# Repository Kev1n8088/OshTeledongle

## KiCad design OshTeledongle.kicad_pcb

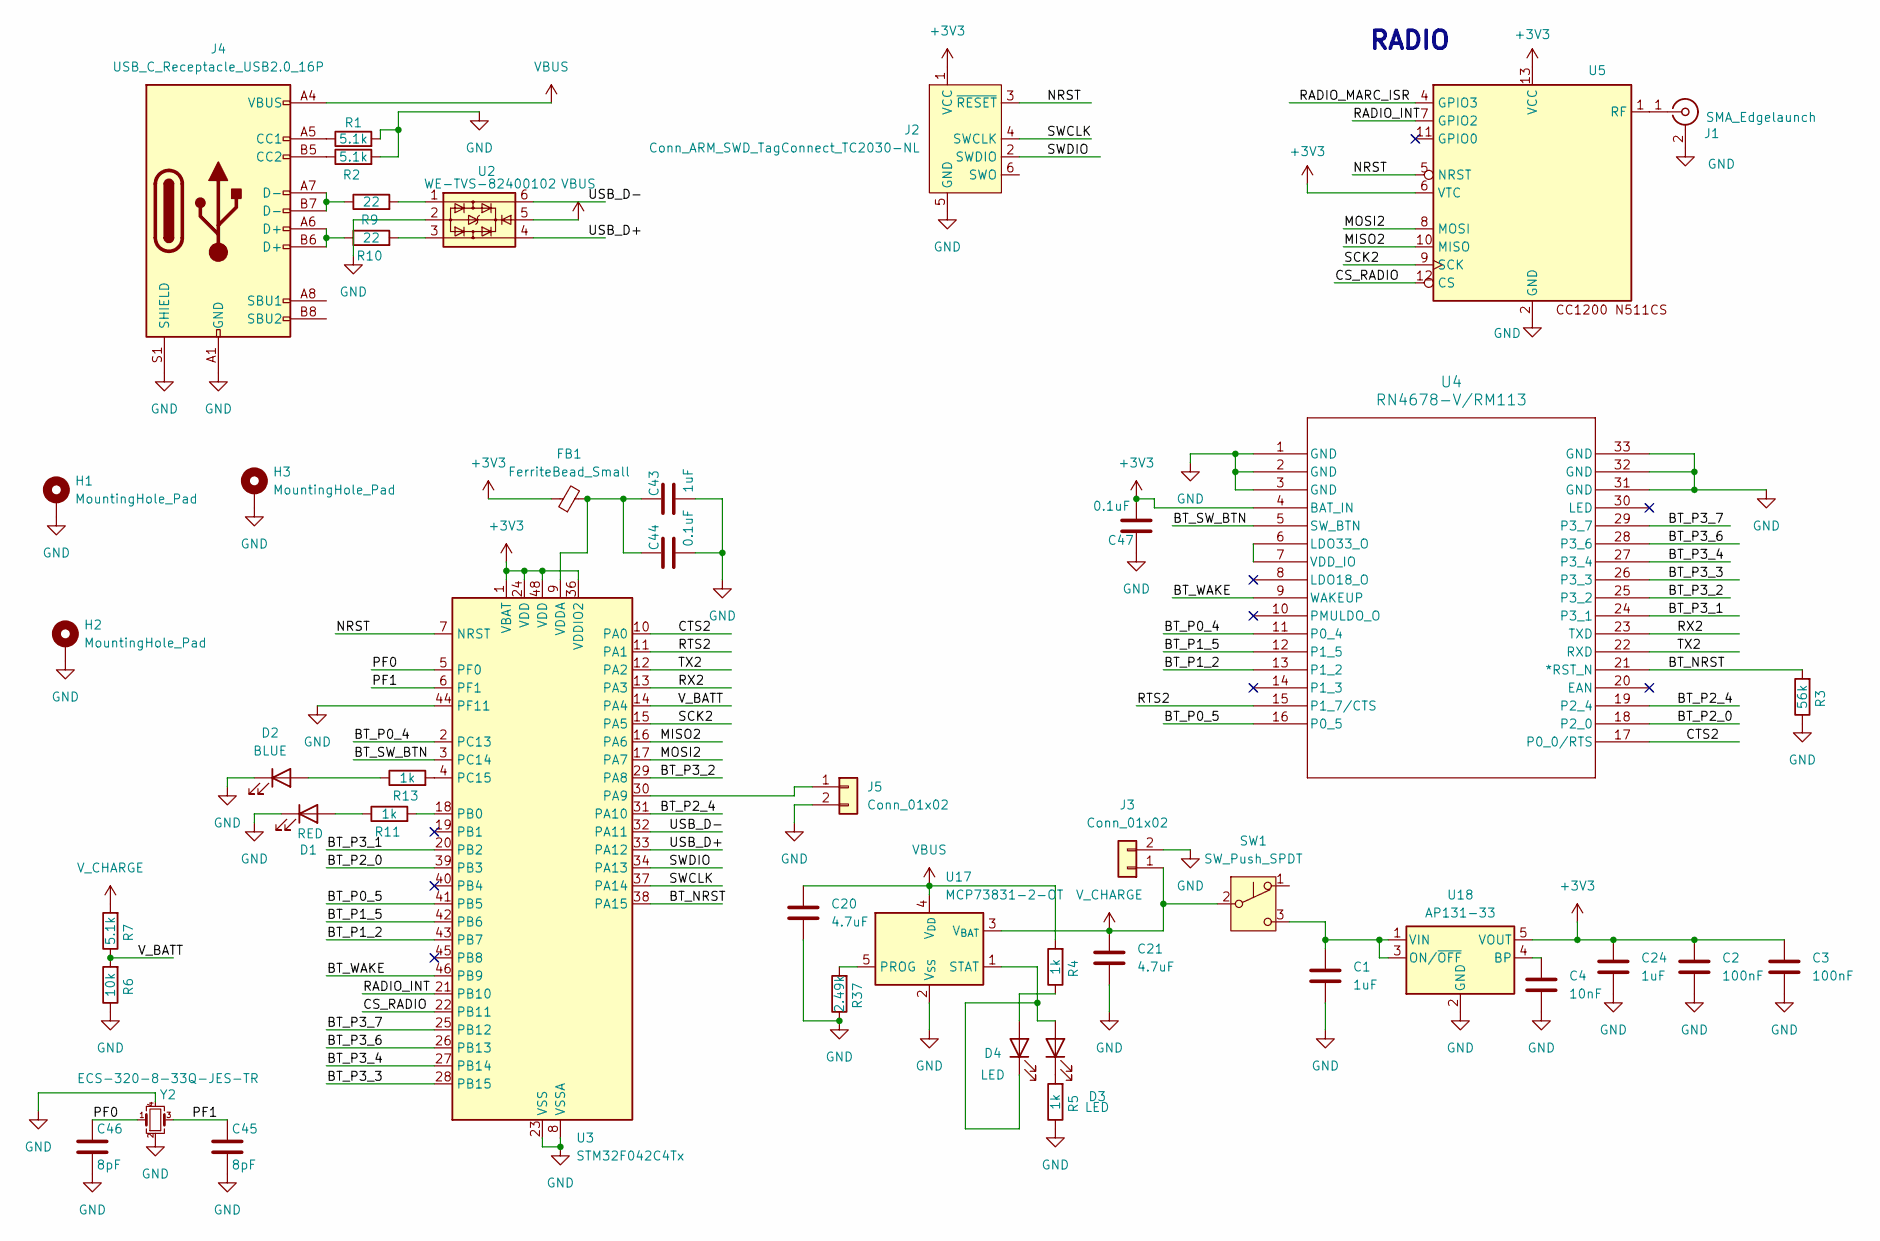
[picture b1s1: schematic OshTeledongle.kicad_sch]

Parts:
C1, C24, C43: 1uF; C_0402_1005Metric
C2, C3: 100nF; C_0402_1005Metric
C4: 10nF; C_0402_1005Metric
C20, C21: 4.7uF; C_0402_1005Metric
C44, C47: 0.1uF; C_0402_1005Metric
C45, C46: 8pF; C_0402_1005Metric
D1: RED; LED_0603_1608Metric
D2: BLUE; LED_0603_1608Metric
D3, D4: LED; LED_0603_1608Metric
FB1: FerriteBead_Small; L_0402_1005Metric
H1, H2, H3: MountingHole_Pad; MountingHole_3.2mm_M3_DIN965_Pad
J1: SMA_Edgelaunch; SMA_Amphenol_132289_EdgeMount
J2: Conn_ARM_SWD_TagConnect_TC2030-NL; Tag-Connect_TC2030-IDC-NL_2x03_P1.27mm_Vertical
J3: Conn_01x02; JST_PH_S2B-PH-K_1x02_P2.00mm_Horizontal
J4: USB_C_Receptacle_USB2.0_16P; USB_C_Receptacle_GCT_USB4105-xx-A_16P_TopMnt_Horizontal
J5: Conn_01x02; PinHeader_1x02_P2.54mm_Vertical
R1, R2, R7: 5.1k; R_0402_1005Metric
R3: 56k; R_0402_1005Metric
R4, R5, R11, R13: 1k; R_0402_1005Metric
R6: 10k; R_0402_1005Metric
R9, R10: 22; R_0402_1005Metric
R37: 2.49k; R_0402_1005Metric
SW1: SW_Push_SPDT; SW_E-Switch_EG1224_SPDT_Angled
U2: WE-TVS-82400102; SOT-23-6
U3: STM32F042C4Tx; LQFP-48_7x7mm_P0.5mm
U4: RN4678-V/RM113; RN4678_MCH
U5: N511CS
U17: MCP73831-2-OT; SOT-23-5
U18: AP131-33; SOT-23-5
Y2: ECS-320-8-33Q-JES-TR; Crystal_SMD_Abracon_ABM8G-4Pin_3.2x2.5mm

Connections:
+3V3: C2.2, C3.2, C24.2, C47.1, FB1.1, J2.1 (VCC), U3.1 (VBAT), U3.24 (VDD), U3.36 (VDDIO2), U3.48 (VDD), U4.4 (BAT_IN), U5.6 (VTC), U5.13 (VCC), U18.5 (VOUT)
/BT_NRST: R3.2, U3.38 (PA15), U4.21 (*RST_N)
/BT_P0_4: U3.2 (PC13), U4.11 (P0_4)
/BT_P0_5: U3.41 (PB5), U4.16 (P0_5)
/BT_P1_2: U3.43 (PB7), U4.13 (P1_2)
/BT_P1_5: U3.42 (PB6), U4.12 (P1_5)
/BT_P2_0: U3.39 (PB3), U4.18 (P2_0)
/BT_P2_4: U3.31 (PA10), U4.19 (P2_4)
/BT_P3_1: U3.20 (PB2), U4.24 (P3_1)
/BT_P3_2: U3.29 (PA8), U4.25 (P3_2)
/BT_P3_3: U3.28 (PB15), U4.26 (P3_3)
/BT_P3_4: U3.27 (PB14), U4.27 (P3_4)
/BT_P3_6: U3.26 (PB13), U4.28 (P3_6)
/BT_P3_7: U3.25 (PB12), U4.29 (P3_7)
/BT_SW_BTN: U3.3 (PC14), U4.5 (SW_BTN)
/BT_WAKE: U3.46 (PB9), U4.9 (WAKEUP)
/CS_RADIO: U3.22 (PB11), U5.12 (CS)
/CTS2: U3.10 (PA0), U4.17 (P0_0/RTS)
/MISO2: U3.16 (PA6), U5.10 (MISO)
/MOSI2: U3.17 (PA7), U5.8 (MOSI)
/NRST: J2.3 (~RESET), U3.7 (NRST), U5.5 (NRST)
/PF0: C46.2, U3.5 (PF0), Y2.1
/PF1: C45.2, U3.6 (PF1), Y2.3
/RADIO_INT: U3.21 (PB10), U5.7 (GPIO2)
/RADIO_MARC_ISR: U5.4 (GPIO3)
/RTS2: U3.11 (PA1), U4.15 (P1_7/CTS)
/RX2: U3.13 (PA3), U4.23 (TXD)
/SCK2: U3.15 (PA5), U5.9 (SCK)
/SWCLK: J2.4 (SWCLK), U3.37 (PA14)
/SWDIO: J2.2 (SWDIO), U3.34 (PA13)
/TX2: U3.12 (PA2), U4.22 (RXD)
/USB_D+: U2.4, U3.33 (PA12)
/USB_D-: U2.6, U3.32 (PA11)
/V_BATT: R6.2, R7.1, U3.14 (PA4)
GND: C1.1, C2.1, C3.1, C4.1, C20.1, C21.1, C24.1, C43.1, C44.1, C45.1, C46.1, C47.2, D1.1 (K), D2.1 (K), H1.1, H2.1, H3.1, J1.2 (Ext), J2.5 (GND), J3.2, J4.A1 (GND), J4.A12 (GND), J4.B1 (GND), J4.B12 (GND), J4.S1 (SHIELD), J5.2, R1.2, R2.2, R3.1, R5.1, R6.1, R37.1, U2.2, U3.8 (VSSA), U3.23 (VSS), U3.35 (VSS), U3.44 (PF11), U3.47 (VSS), U4.1 (GND), U4.2 (GND), U4.3 (GND), U4.31 (GND), U4.32 (GND), U4.33 (GND), U5.2 (GND), U5.3 (GND), U5.14 (GND), U17.2 (V_{SS}), U18.2 (GND), Y2.2, Y2.4
unnamed: D1.2 (A), R11.1
unnamed: D2.2 (A), R13.1
unnamed: D3.2 (A), D4.1 (K), U17.1 (STAT)
unnamed: D3.1 (K), R5.2
unnamed: D4.2 (A), R4.1
unnamed: J1.1 (In), U5.1 (RF)
unnamed: J4.A5 (CC1), R1.1
unnamed: J4.B5 (CC2), R2.1
unnamed: J4.A6 (D+), J4.B6 (D+), R10.1
unnamed: J4.A7 (D-), J4.B7 (D-), R9.1
unnamed: J5.1, U3.30 (PA9)
unnamed: R9.2, U2.1
unnamed: R10.2, U2.3
unnamed: C1.2, SW1.3 (C), U18.1 (VIN), U18.3 (ON/~OFF)
unnamed: R11.2, U3.18 (PB0)
unnamed: R13.2, U3.4 (PC15)
unnamed: C43.2, C44.2, FB1.2, U3.9 (VDDA)
unnamed: U4.6 (LDO33_O), U4.7 (VDD_IO)
unnamed: R37.2, U17.5 (PROG)
unnamed: C4.2, U18.4 (BP)
VBUS: C20.2, J4.A4 (VBUS), J4.A9 (VBUS), J4.B4 (VBUS), J4.B9 (VBUS), R4.2, U2.5, U17.4 (V_{DD})
V_CHARGE: C21.2, J3.1, R7.2, SW1.2 (B), U17.3 (V_{BAT})

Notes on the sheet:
RADIO

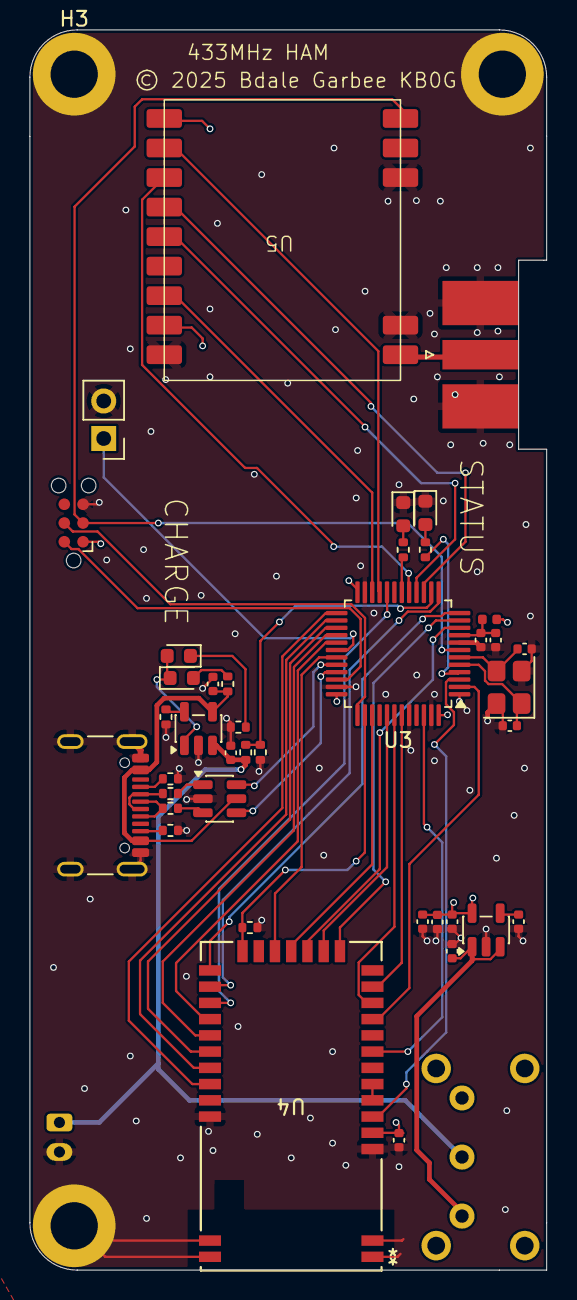
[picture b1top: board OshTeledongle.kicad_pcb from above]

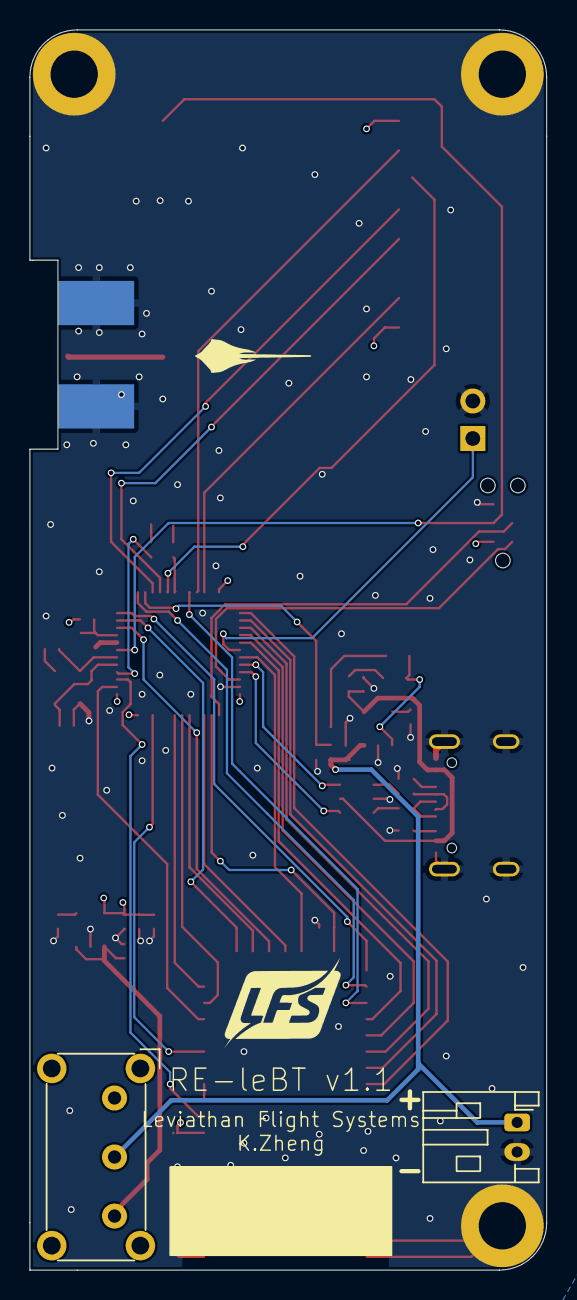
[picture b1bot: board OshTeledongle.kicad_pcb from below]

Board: 4 copper layers, 35.0 x 84.0 mm, 45 parts (2 on the bottom side), 56 nets.

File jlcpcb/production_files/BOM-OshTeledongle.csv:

Comment,Designator,Footprint,LCSC,Quantity
0.1uF,"C44,C47",C_0402_1005Metric,C1525,2
100nF,"C2,C3",C_0402_1005Metric,C1525,2
10k,R6,R_0402_1005Metric,C25744,1
10nF,C4,C_0402_1005Metric,C15195,1
1k,"R11,R13,R4,R5",R_0402_1005Metric,C11702,4
1uF,"C1,C24,C43",C_0402_1005Metric,C52923,3
2.49k,R37,R_0402_1005Metric,C145071,1
22,"R10,R9",R_0402_1005Metric,C25092,2
4.7uF,"C20,C21",C_0402_1005Metric,C23733,2
5.1k,"R1,R2,R7",R_0402_1005Metric,C25905,3
56k,R3,R_0402_1005Metric,C25794,1
8pF,"C45,C46",C_0402_1005Metric,C1549,2
AP131-33,U18,SOT-23-5,C6864,1
BLUE,D2,LED_0603_1608Metric,C2290,1
ECS-320-8-33Q-JES-TR,Y2,Crystal_SMD_Abracon_ABM8G-4Pin_3.2x2.5mm,C3034370,1
FerriteBead_Small,FB1,L_0402_1005Metric,C269768,1
LED,D3,LED_0603_1608Metric,C2286,1
LED,D4,LED_0603_1608Metric,C2290,1
MCP73831-2-OT,U17,SOT-23-5,C424093,1
RED,D1,LED_0603_1608Metric,C2286,1
STM32F042C4Tx,U3,LQFP-48_7x7mm_P0.5mm,C88447,1
USB_C_Receptacle_USB2.0_16P,J4,USB_C_Receptacle_GCT_USB4105-xx-A_16P_TopMnt_Horizontal,C3020560,1
WE-TVS-82400102,U2,SOT-23-6,C1975330,1
Conn_01x02,J3,JST_PH_S2B-PH-K_1x02_P2.00mm_Horizontal,,1
RN4678-V/RM113,U4,RN4678_MCH,,1
SW_Push_SPDT,SW1,SW_E-Switch_EG1224_SPDT_Angled,,1
~,U5,N511CS,,1
SMA_Edgelaunch,J1,SMA_Amphenol_132289_EdgeMount,,1
Conn_01x02,J5,PinHeader_1x02_P2.54mm_Vertical,,1

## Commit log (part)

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2025-10-20 v1.0 done
2026-05-18 v1.0 sent to fab

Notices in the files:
OshTeledongle.kicad_pcb:
© 2025 Bdale Garbee KB0G
